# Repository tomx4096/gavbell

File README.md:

Detect wielders of weird cables

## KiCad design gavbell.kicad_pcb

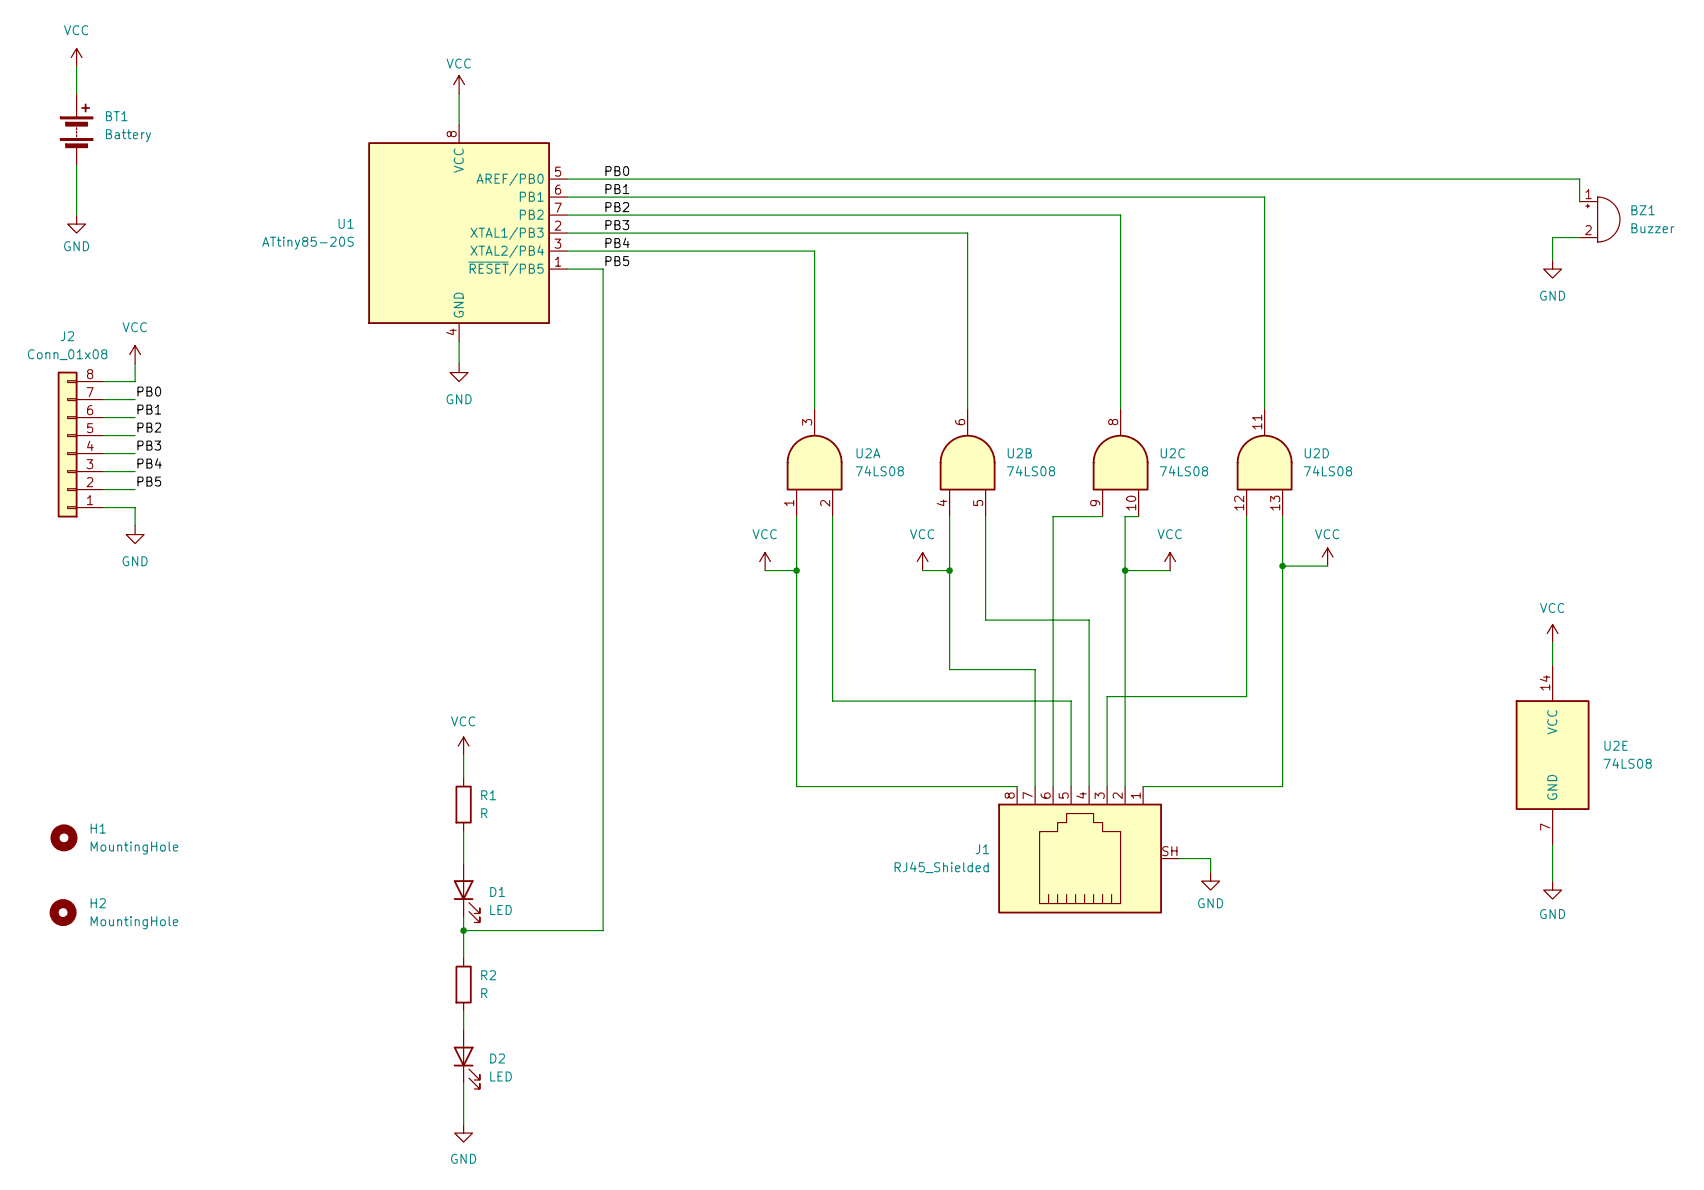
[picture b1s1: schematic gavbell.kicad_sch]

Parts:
BT1: Battery; BatteryHolder_Keystone_2462_2xAA
BZ1: Buzzer; Buzzer_15x7.5RM7.6
D1, D2: LED; LED_1812_4532Metric
H1, H2: MountingHole; MountingHole_3.2mm_M3
J1: RJ45_Shielded; RJ45_Amphenol_RJHSE5380
J2: Conn_01x08; PinHeader_1x08_P2.54mm_Vertical
R1, R2: R; R_1812_4532Metric
U1: ATtiny85-20S; SOIC-8W_5.3x5.3mm_P1.27mm
U2: 74LS08; TSSOP-14_4.4x5mm_P0.65mm

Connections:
/PB0: BZ1.1 (-), J2.7, U1.5 (AREF/PB0)
/PB1: J2.6, U1.6 (PB1), U2.11
/PB2: J2.5, U1.7 (PB2), U2.8
/PB3: J2.4, U1.2 (XTAL1/PB3), U2.6
/PB4: J2.3, U1.3 (XTAL2/PB4), U2.3
/PB5: D1.1 (K), J2.2, R2.1, U1.1 (~RESET/PB5)
GND: BT1.2 (-), BZ1.2 (+), D2.1 (K), J1.SH, J2.1, U1.4 (GND), U2.7 (GND)
unnamed: D1.2 (A), R1.2
unnamed: D2.2 (A), R2.2
unnamed: J1.3, U2.12
unnamed: J1.4, U2.5
unnamed: J1.5, U2.2
unnamed: J1.6, U2.9
VCC: BT1.1 (+), J1.1, J1.2, J1.7, J1.8, J2.8, R1.1, U1.8 (VCC), U2.1, U2.4, U2.10, U2.13, U2.14 (VCC)

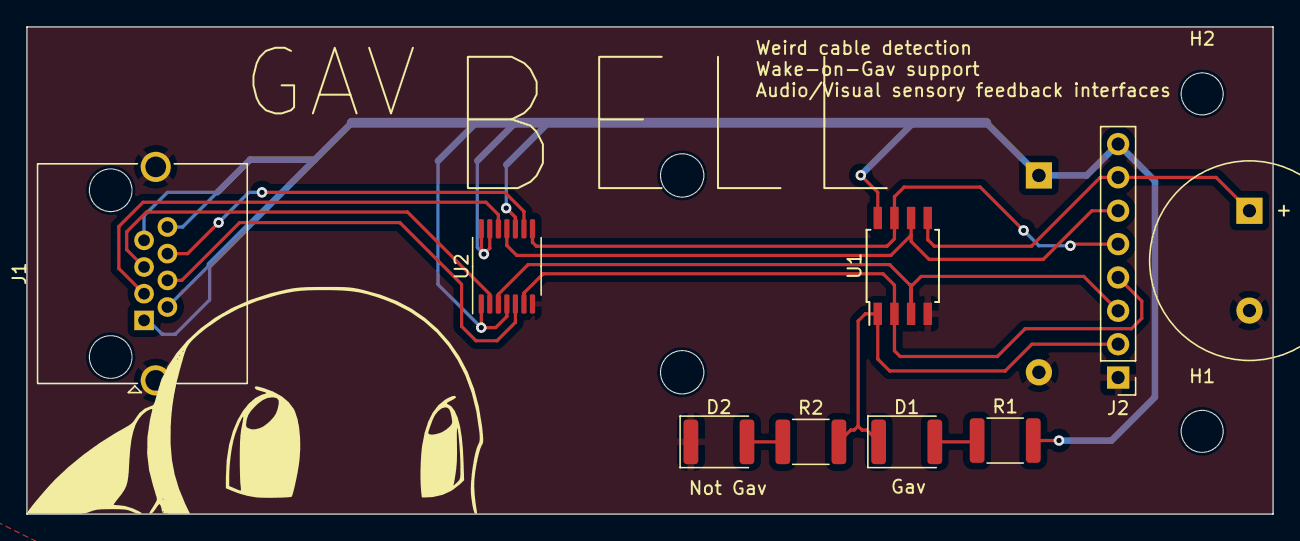
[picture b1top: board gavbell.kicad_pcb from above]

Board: 2 copper layers, 94.9 x 37.1 mm, 12 parts (1 on the bottom side), 14 nets.

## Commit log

2024-01-15 init
